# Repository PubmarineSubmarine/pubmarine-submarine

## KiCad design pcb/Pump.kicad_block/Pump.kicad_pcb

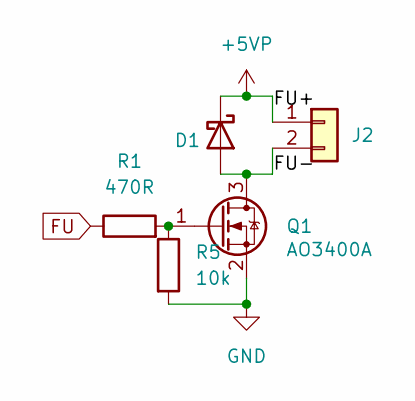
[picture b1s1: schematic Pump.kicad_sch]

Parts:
D1: B5819W; D_SOD-123
J2: Conn_01x02; JST_PH_B2B-PH-K_1x02_P2.00mm_Vertical
Q1: AO3400A; SOT-23_Handsoldering
R1: 470R; R_0603_1608Metric_Pad0.98x0.95mm_HandSolder
R5: 10k; R_0603_1608Metric_Pad0.98x0.95mm_HandSolder

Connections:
+5VP: D1.1 (K), J2.1
/FU-: D1.2 (A), J2.2, Q1.3 (D)
FU: R1.1
GND: Q1.2 (S), R5.2
unnamed: Q1.1 (G), R1.2, R5.1

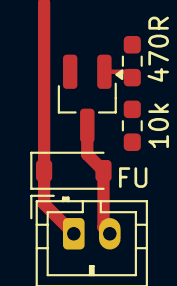
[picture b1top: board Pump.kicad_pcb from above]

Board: 2 copper layers, 5 parts (0 on the bottom side), 4 nets.

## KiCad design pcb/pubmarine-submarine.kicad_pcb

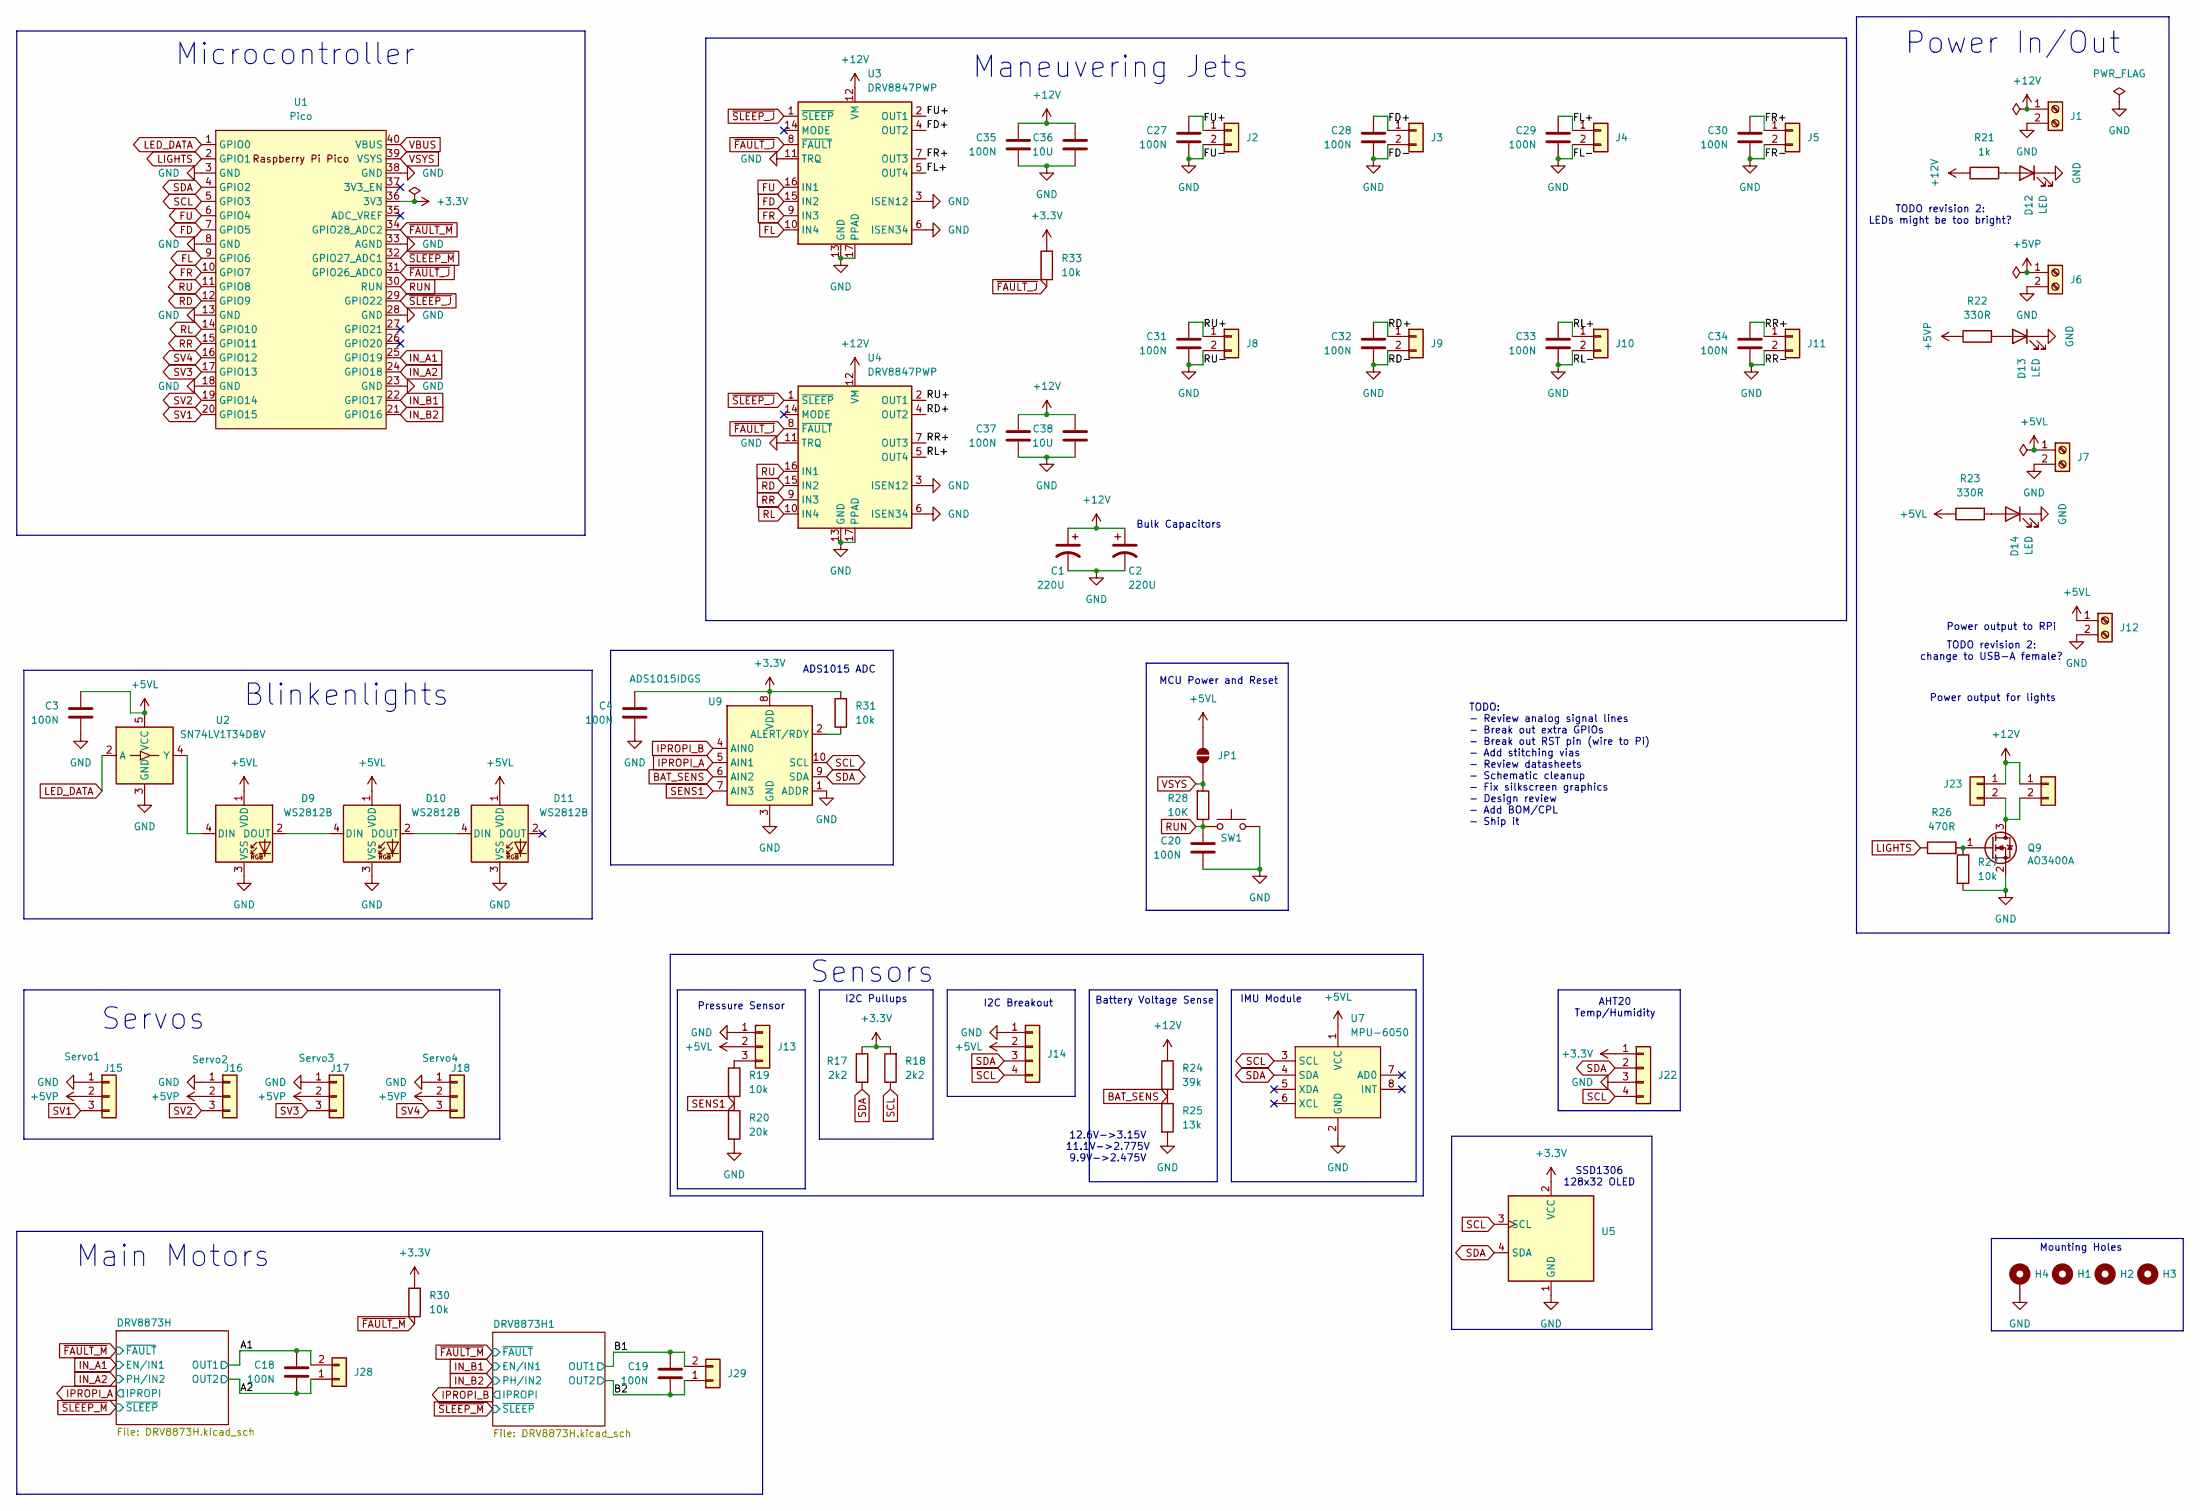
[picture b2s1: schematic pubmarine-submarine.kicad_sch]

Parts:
C1, C2: 220U; CP_Radial_D6.3mm_P2.50mm
C3, C4, C18, C19, C20, C27, C28, C29, C30, C31, C32, C33, C34, C35, C37: 100N; C_0603_1608Metric_Pad1.08x0.95mm_HandSolder
C36, C38: 10U; C_0603_1608Metric_Pad1.08x0.95mm_HandSolder
D9, D10, D11: WS2812B; LED_WS2812B_PLCC4_5.0x5.0mm_P3.2mm
D12, D13, D14: LED; LED_0603_1608Metric_Pad1.05x0.95mm_HandSolder
H1, H2, H3: MountingHole; MountingHole_2.2mm_M2
H4: MountingHole_Pad; MountingHole_2.2mm_M2_Pad
J1, J6, J7, J12: Screw_Terminal_01x02; TerminalBlock_Altech_AK300-2_P5.00mm
J2, J3, J4, J5, J8, J9, J10, J11, J23, J24: Conn_01x02; JST_PH_B2B-PH-K_1x02_P2.00mm_Vertical
J13: Conn_01x03; JST_PH_B3B-PH-K_1x03_P2.00mm_Vertical
J14: Conn_01x04; JST_PH_B4B-PH-K_1x04_P2.00mm_Vertical
J15: Servo1; JST_PH_B3B-PH-K_1x03_P2.00mm_Vertical
J16: Servo2; JST_PH_B3B-PH-K_1x03_P2.00mm_Vertical
J17: Servo3; JST_PH_B3B-PH-K_1x03_P2.00mm_Vertical
J18: Servo4; JST_PH_B3B-PH-K_1x03_P2.00mm_Vertical
J22: Conn_01x04; PinHeader_1x04_P2.54mm_Vertical
J28, J29: Conn_01x02; TerminalBlock_Altech_AK300-2_P5.00mm
JP1: Jumper_2_Open; SolderJumper-2_P1.3mm_Open_RoundedPad1.0x1.5mm
Q9: AO3400A; SOT-23_Handsoldering
R17, R18: 2k2; R_0603_1608Metric_Pad0.98x0.95mm_HandSolder
R19, R27, R30, R31, R33: 10k; R_0603_1608Metric_Pad0.98x0.95mm_HandSolder
R20: 20k; R_0603_1608Metric_Pad0.98x0.95mm_HandSolder
R21: 1k; R_0603_1608Metric_Pad0.98x0.95mm_HandSolder
R22, R23: 330R; R_0603_1608Metric_Pad0.98x0.95mm_HandSolder
R24: 39k; R_0603_1608Metric_Pad0.98x0.95mm_HandSolder
R25: 13k; R_0603_1608Metric_Pad0.98x0.95mm_HandSolder
R26: 470R; R_0603_1608Metric_Pad0.98x0.95mm_HandSolder
R28: 10K; R_0603_1608Metric_Pad0.98x0.95mm_HandSolder
SW1: SW_Push; SW_PUSH_6mm
U1: Pico; RPi_Pico_SMD_TH
U2: SN74LV1T34DBV; SOT-23-5
U3, U4: DRV8847PWP; HTSSOP-16-1EP_4.4x5mm_P0.65mm_EP3.4x5mm_Mask2.46x2.31mm_The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
U5: ER_OLEDM0.91_1x-I2C
U7: MPU-6050; MPU-6050_Module
U9: ADS1015IDGS; TSSOP-10_3x3mm_P0.5mm

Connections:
+5VP: J6.1, J15.2, J16.2, J17.2, J18.2, R22.1
+12V: C1.1, C2.1, C35.1, C36.1, C37.1, C38.1, J1.1, J23.1, J24.1, R21.1, R24.1, U3.12 (VM), U4.12 (VM); also elsewhere on the board
/A1: C18.1, J28.2; also elsewhere on the board
/A2: C18.2, J28.1; also elsewhere on the board
/B1: C19.1, J29.2; also elsewhere on the board
/B2: C19.2, J29.1; also elsewhere on the board
/FD+: C28.1, J3.1, U3.4 (OUT2)
/FL+: C29.1, J4.1, U3.5 (OUT4)
/FR+: C30.1, J5.1, U3.7 (OUT3)
/FU+: C27.1, J2.1, U3.2 (OUT1)
/RD+: C32.1, J9.1, U4.4 (OUT2)
/RL+: C33.1, J10.1, U4.5 (OUT4)
/RR+: C34.1, J11.1, U4.7 (OUT3)
/RU+: C31.1, J8.1, U4.2 (OUT1)
BAT_SENS: R24.2, R25.1, U9.6 (AIN2)
FD: U1.7 (GPIO5), U3.15 (IN2)
FL: U1.9 (GPIO6), U3.10 (IN4)
FR: U1.10 (GPIO7), U3.9 (IN3)
FU: U1.6 (GPIO4), U3.16 (IN1)
GND: C1.2, C2.2, C3.2, C4.2, C20.2, C27.2, C28.2, C29.2, C30.2, C31.2, C32.2, C33.2, C34.2, C35.2, C36.2, C37.2, C38.2, D9.3 (VSS), D10.3 (VSS), D11.3 (VSS), D12.1 (K), D13.1 (K), D14.1 (K), H4.1 (1_1), J1.2, J2.2, J3.2, J4.2, J5.2, J6.2, J7.2, J8.2, J9.2, J10.2, J11.2, J12.2, J13.1, J14.1, J15.1, J16.1, J17.1, J18.1, J22.3, Q9.2 (S), R20.2, R25.2, R27.2, SW1.2, U1.3 (GND), U1.8 (GND), U1.13 (GND), U1.18 (GND), U1.23 (GND), U1.28 (GND), U1.33 (AGND), U1.38 (GND), U2.3 (GND), U3.3 (ISEN12), U3.6 (ISEN34), U3.11 (TRQ), U3.13 (GND), U3.17 (PPAD), U4.3 (ISEN12), U4.6 (ISEN34), U4.11 (TRQ), U4.13 (GND), U4.17 (PPAD), U5.1 (GND), U7.2 (GND), U9.1 (ADDR), U9.3 (GND); also elsewhere on the board
IN_A1: U1.25 (GPIO19); also elsewhere on the board
IN_A2: U1.24 (GPIO18); also elsewhere on the board
IN_B1: U1.22 (GPIO17); also elsewhere on the board
IN_B2: U1.21 (GPIO16); also elsewhere on the board
IPROPI_A: U9.5 (AIN1); also elsewhere on the board
IPROPI_B: U9.4 (AIN0); also elsewhere on the board
LED_DATA: U1.1 (GPIO0), U2.2 (A)
LIGHTS: R26.1, U1.2 (GPIO1)
unnamed: D9.4 (DIN), U2.4 (Y)
unnamed: D9.2 (DOUT), D10.4 (DIN)
unnamed: D10.2 (DOUT), D11.4 (DIN)
unnamed: D12.2 (A), R21.2
unnamed: D13.2 (A), R22.2
unnamed: D14.2 (A), R23.2
unnamed: J13.3, R19.1
unnamed 37: U1.32 (GPIO27_ADC1); also elsewhere on the board
unnamed: J23.2, J24.2, Q9.3 (D)
unnamed: Q9.1 (G), R26.2, R27.1
unnamed: R31.1, U9.2 (ALERT/RDY)
RD: U1.12 (GPIO9), U4.15 (IN2)
RL: U1.14 (GPIO10), U4.10 (IN4)
RR: U1.15 (GPIO11), U4.9 (IN3)
RU: U1.11 (GPIO8), U4.16 (IN1)
RUN: C20.1, R28.1, SW1.1, U1.30 (RUN); also elsewhere on the board
SCL: J14.4, J22.4, R18.1, U1.5 (GPIO3), U5.3 (SCL), U7.3 (SCL), U9.10 (SCL)
SDA: J14.3, J22.2, R17.1, U1.4 (GPIO2), U5.4 (SDA), U7.4 (SDA), U9.9 (SDA)
SENS1: R19.2, R20.1, U9.7 (AIN3)
SV1: J15.3, U1.20 (GPIO15)
SV2: J16.3, U1.19 (GPIO14)
SV3: J17.3, U1.17 (GPIO13)
SV4: J18.3, U1.16 (GPIO12)
VBUS: U1.40 (VBUS)
VSYS: JP1.1 (A), R28.2, U1.39 (VSYS)
~FAULT_M: R30.2, U1.34 (GPIO28_ADC2); also elsewhere on the board

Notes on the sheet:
TODO revision 2: LEDs might be too bright?
Pressure Sensor
Bulk Capacitors
Sensors
ADS1015 ADC
Power output to RPi
TODO: - Review analog signal lines - Break out extra GPIOs - Break out RST pin (wire to Pi) - Add stitching vias - Review datasheets - Schematic cleanup - Fix silkscreen graphics - Design review - Add BOM/CPL - Ship it
IMU Module
Main Motors
I2C Breakout
MCU Power and Reset
Servos
Battery Voltage Sense
SSD1306 128x32 OLED
Power In/Out
I2C Pullups
Microcontroller
12.6V->3.15V 11.1V->2.775V 9.9V->2.475V
TODO revision 2: change to USB-A female?
AHT20 Temp/Humidity
Mounting Holes
Maneuvering Jets
Power output for lights
Blinkenlights

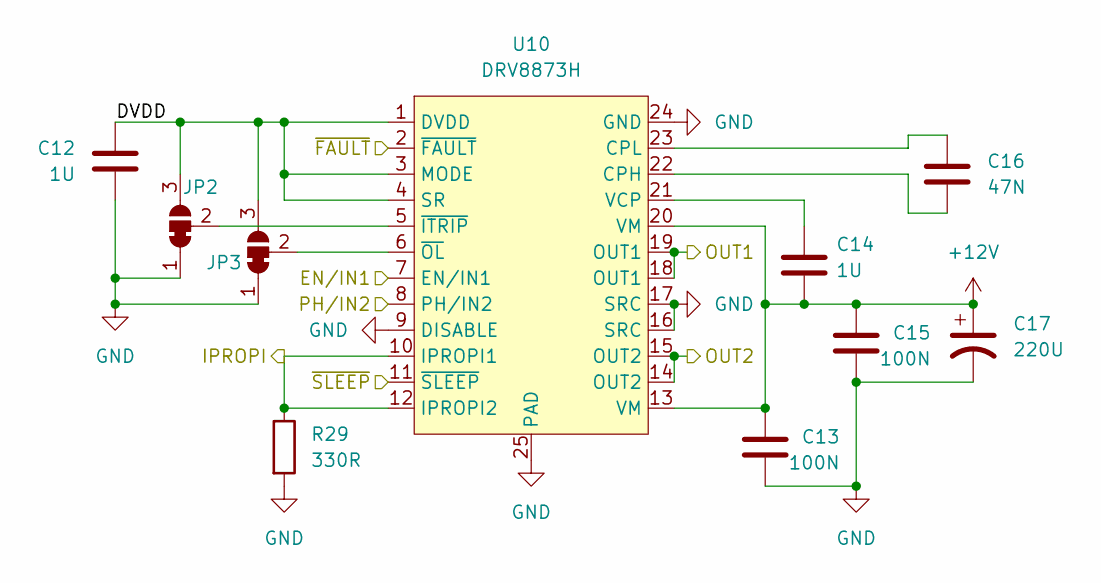
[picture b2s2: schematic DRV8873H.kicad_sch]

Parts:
C12, C14: 1U; C_0603_1608Metric_Pad1.08x0.95mm_HandSolder
C13, C15: 100N; C_0603_1608Metric_Pad1.08x0.95mm_HandSolder
C16: 47N; C_0603_1608Metric_Pad1.08x0.95mm_HandSolder
C17: 220U; CP_Radial_D6.3mm_P2.50mm
JP2, JP3: SolderJumper_3_Bridged12; SolderJumper-3_P1.3mm_Bridged12_RoundedPad1.0x1.5mm
R29: 330R; R_0603_1608Metric_Pad0.98x0.95mm_HandSolder
U10: DRV8873H; HTSSOP-24-1EP_4.4x7.8mm_P0.65mm_EP3.4x7.8mm_Mask2.44x3.42mm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

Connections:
+12V: C13.1, C14.2, C15.1, C17.1, U10.13 (VM), U10.20 (VM); also elsewhere on the board
/A1: U10.18 (OUT1), U10.19 (OUT1); also elsewhere on the board
/A2: U10.14 (OUT2), U10.15 (OUT2); also elsewhere on the board
/DRV8873H/DVDD: C12.1, JP2.3 (B), JP3.3 (B), U10.1 (DVDD), U10.3 (MODE), U10.4 (SR)
GND: C12.2, C13.2, C15.2, C17.2, JP2.1 (A), JP3.1 (A), R29.2, U10.9 (DISABLE), U10.16 (SRC), U10.17 (SRC), U10.24 (GND), U10.25 (PAD); also elsewhere on the board
IN_A1: U10.7 (EN/IN1); also elsewhere on the board
IN_A2: U10.8 (PH/IN2); also elsewhere on the board
IPROPI_A: R29.1, U10.10 (IPROPI1), U10.12 (IPROPI2); also elsewhere on the board
unnamed: JP2.2 (C), U10.5 (~ITRIP)
unnamed: JP3.2 (C), U10.6 (~OL)
unnamed: C16.2, U10.22 (CPH)
unnamed: C16.1, U10.23 (CPL)
unnamed: C14.1, U10.21 (VCP)
~FAULT_M: U10.2 (~FAULT); also elsewhere on the board

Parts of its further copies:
C21, C23: 1U; C_0603_1608Metric_Pad1.08x0.95mm_HandSolder
C22, C24: 100N; C_0603_1608Metric_Pad1.08x0.95mm_HandSolder
C25: 47N; C_0603_1608Metric_Pad1.08x0.95mm_HandSolder
C26: 220U; CP_Radial_D6.3mm_P2.50mm
JP4, JP5: SolderJumper_3_Bridged12; SolderJumper-3_P1.3mm_Bridged12_RoundedPad1.0x1.5mm
R32: 330R; R_0603_1608Metric_Pad0.98x0.95mm_HandSolder
U11: DRV8873H; HTSSOP-24-1EP_4.4x7.8mm_P0.65mm_EP3.4x7.8mm_Mask2.44x3.42mm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

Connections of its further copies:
+12V: C22.1, C23.2, C24.1, C26.1, U11.13 (VM), U11.20 (VM); also elsewhere on the board
/B1: U11.18 (OUT1), U11.19 (OUT1); also elsewhere on the board
/B2: U11.14 (OUT2), U11.15 (OUT2); also elsewhere on the board
/DRV8873H1/DVDD: C21.1, JP4.3 (B), JP5.3 (B), U11.1 (DVDD), U11.3 (MODE), U11.4 (SR)
GND: C21.2, C22.2, C24.2, C26.2, JP4.1 (A), JP5.1 (A), R32.2, U11.9 (DISABLE), U11.16 (SRC), U11.17 (SRC), U11.24 (GND), U11.25 (PAD); also elsewhere on the board
IN_B1: U11.7 (EN/IN1); also elsewhere on the board
IN_B2: U11.8 (PH/IN2); also elsewhere on the board
IPROPI_B: R32.1, U11.10 (IPROPI1), U11.12 (IPROPI2); also elsewhere on the board
unnamed: JP4.2 (C), U11.5 (~ITRIP)
unnamed: JP5.2 (C), U11.6 (~OL)
unnamed: C25.2, U11.22 (CPH)
unnamed: C25.1, U11.23 (CPL)
unnamed: C23.1, U11.21 (VCP)
~FAULT_M: U11.2 (~FAULT); also elsewhere on the board

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
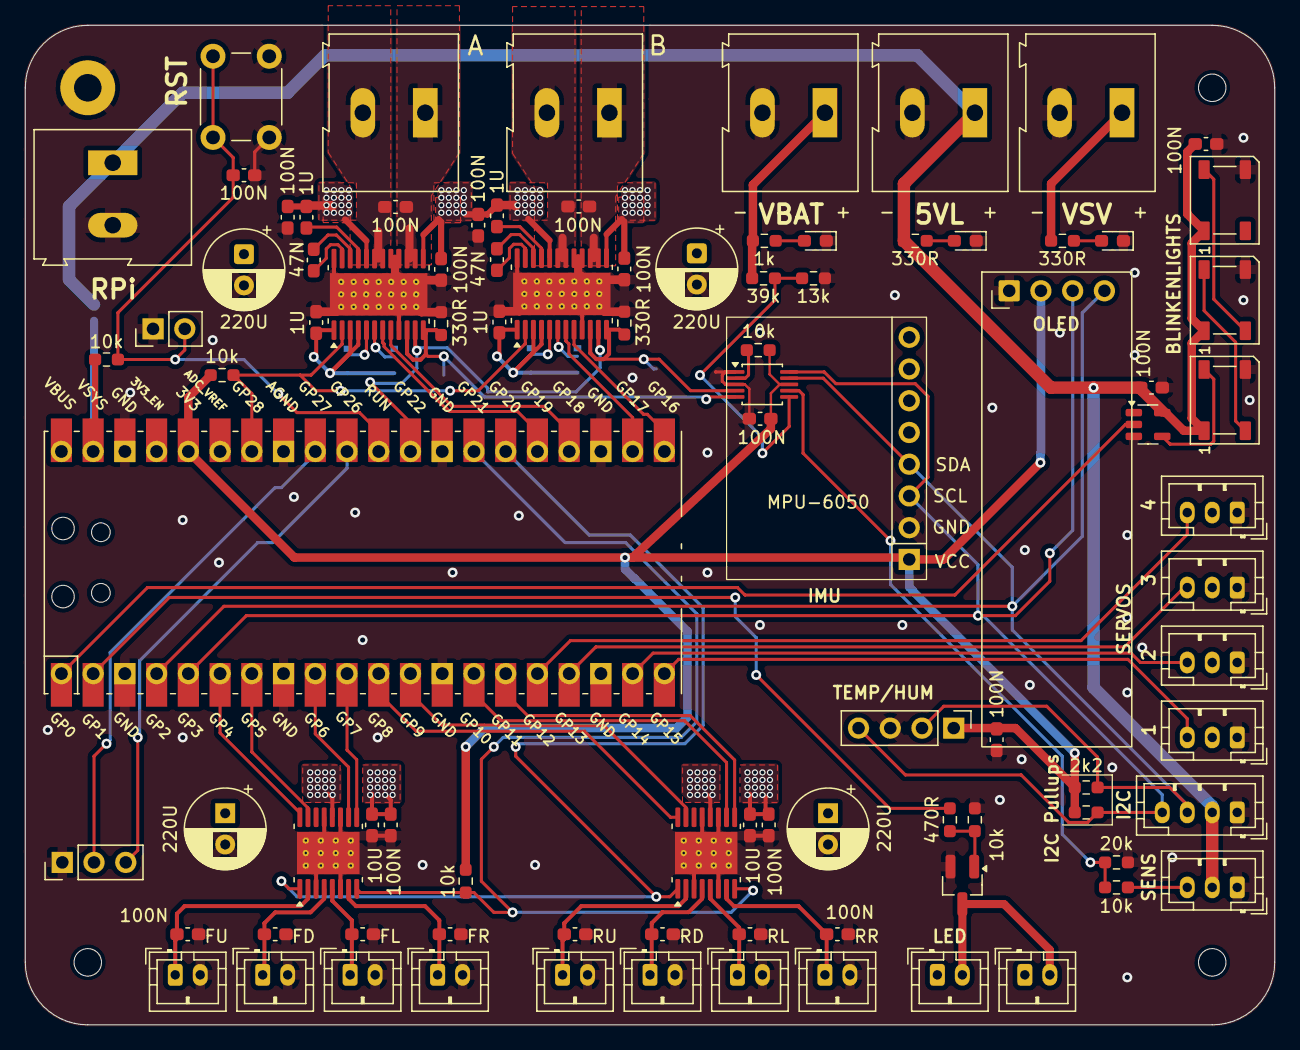
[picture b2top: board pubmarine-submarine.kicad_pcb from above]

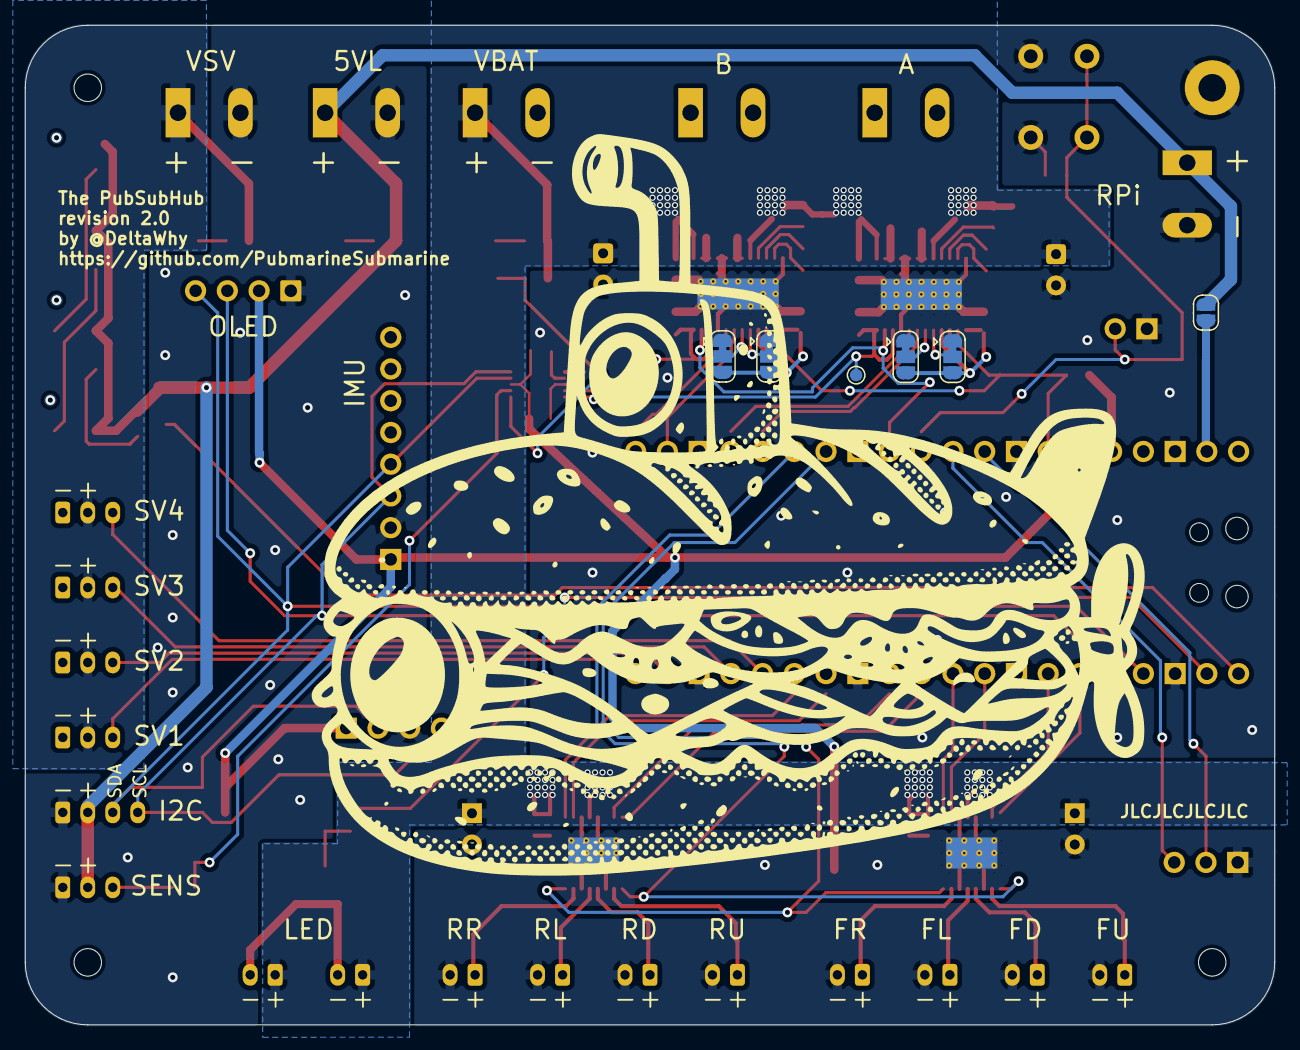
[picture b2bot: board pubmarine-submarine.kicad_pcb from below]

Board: 4 copper layers, 100.0 x 80.0 mm, 103 parts (7 on the bottom side), 71 nets.

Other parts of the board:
C5, C6: 100N; C_0603_1608Metric_Pad1.08x0.95mm_HandSolder
J19: Conn_01x03_Pin; PinHeader_1x03_P2.54mm_Vertical
J20: Conn_01x02_Pin; PinHeader_1x02_P2.54mm_Vertical
TP1, TP2: TestPoint; TestPoint_Pad_D1.0mm

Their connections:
GND: C5.2, C6.2, J19.1, J20.1; also elsewhere on the board
IPROPI_A: TP1.1 (1_1); also elsewhere on the board
IPROPI_B: TP2.1 (1_1); also elsewhere on the board
unnamed 37: J19.2; also elsewhere on the board
RUN: J20.2; also elsewhere on the board

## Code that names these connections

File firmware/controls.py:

import board
import pins

import analogio
import digitalio
import pwmio
import busio
import neopixel
import adafruit_mpu6050_patched as adafruit_mpu6050
import adafruit_ads1x15.ads1015
import adafruit_ads1x15.analog_in
import adafruit_ahtx0
import displayio
import i2cdisplaybus
import adafruit_displayio_ssd1306

from adafruit_motor import motor, servo
from config import get_config


# Main motors
_a1 = pwmio.PWMOut(pins.A1, frequency=10000)
_a2 = pwmio.PWMOut(pins.A2, frequency=10000)
_b1 = pwmio.PWMOut(pins.B1, frequency=10000)
_b2 = pwmio.PWMOut(pins.B2, frequency=10000)
motor_a = motor.DCMotor(_a1, _a2)
motor_b = motor.DCMotor(_b1, _b2)
motor_a.decay_mode = motor.FAST_DECAY
motor_b.decay_mode = motor.FAST_DECAY
sleep_m = digitalio.DigitalInOut(pins.SLEEP_M)
sleep_m.switch_to_output()
fault_m = digitalio.DigitalInOut(pins.FAULT_M)
fault_m.switch_to_input()

# Jets
_jet_mapping = get_config().get("jet_mapping", "ABCDEFGH")
_pin_mapping = {"A": pins.FU, "B": pins.FD, "C": pins.FL, "D": pins.FR,
                "E": pins.RU, "F": pins.RD, "G": pins.RL, "H": pins.RR}
jet_fu = digitalio.DigitalInOut(_pin_mapping[_jet_mapping[0]])
jet_fu.switch_to_output()
jet_fd = digitalio.DigitalInOut(_pin_mapping[_jet_mapping[1]])
jet_fd.switch_to_output()
jet_fl = digitalio.DigitalInOut(_pin_mapping[_jet_mapping[2]])
jet_fl.switch_to_output()
jet_fr = digitalio.DigitalInOut(_pin_mapping[_jet_mapping[3]])
jet_fr.switch_to_output()
jet_ru = digitalio.DigitalInOut(_pin_mapping[_jet_mapping[4]])
jet_ru.switch_to_output()
jet_rd = digitalio.DigitalInOut(_pin_mapping[_jet_mapping[5]])
jet_rd.switch_to_output()
jet_rl = digitalio.DigitalInOut(_pin_mapping[_jet_mapping[6]])
jet_rl.switch_to_output()
jet_rr = digitalio.DigitalInOut(_pin_mapping[_jet_mapping[7]])
jet_rr.switch_to_output()
sleep_j = digitalio.DigitalInOut(pins.SLEEP_J)
sleep_j.switch_to_output()
fault_j = digitalio.DigitalInOut(pins.FAULT_J)
fault_j.switch_to_input()

# Servos
_sv1 = pwmio.PWMOut(pins.SV1, frequency=50, duty_cycle=0)
sv1 = servo.Servo(_sv1, min_pulse=500, max_pulse=2500, actuation_range=180)
_sv2 = pwmio.PWMOut(pins.SV2, frequency=50, duty_cycle=0)
sv2 = servo.Servo(_sv2, min_pulse=500, max_pulse=2500, actuation_range=180)
_sv3 = pwmio.PWMOut(pins.SV3, frequency=50, duty_cycle=0)
sv3 = servo.Servo(_sv3, min_pulse=500, max_pulse=2500, actuation_range=180)
_sv4 = pwmio.PWMOut(pins.SV4, frequency=50, duty_cycle=0)
sv4 = servo.Servo(_sv4, min_pulse=500, max_pulse=2500, actuation_range=180)

lights = digitalio.DigitalInOut(pins.LIGHTS)
lights.switch_to_output()

# WS2812B
pixels = neopixel.NeoPixel(pins.LED_DATA, 3)
led = digitalio.DigitalInOut(board.LED)
led.switch_to_output()

# I2C/MPU6050
displayio.release_displays()
i2c = busio.I2C(pins.SCL, pins.SDA, frequency=400000)
mpu = adafruit_mpu6050.MPU6050(i2c)
try:
    ads = adafruit_ads1x15.ads1015.ADS1015(i2c, gain=1, data_rate=1600, mode=adafruit_ads1x15.ads1x15.Mode.SINGLE)
    aht = adafruit_ahtx0.AHTx0(i2c)
    display_bus = i2cdisplaybus.I2CDisplayBus(i2c, device_address=0x3c)
    display = adafruit_displayio_ssd1306.SSD1306(display_bus, width=128, height=32, auto_refresh=False)

    # Analog sensors
    sensor_depth = adafruit_ads1x15.analog_in.AnalogIn(ads, adafruit_ads1x15.ads1015.P3)
    sensor_battery = adafruit_ads1x15.analog_in.AnalogIn(ads, adafruit_ads1x15.ads1015.P2)
    sensor_ipropi_a = adafruit_ads1x15.analog_in.AnalogIn(ads, adafruit_ads1x15.ads1015.P1)
    sensor_ipropi_b = adafruit_ads1x15.analog_in.AnalogIn(ads, adafruit_ads1x15.ads1015.P0)
except ValueError as e:
    import traceback
    traceback.print_exception(e)
    print("Falling back to mocks")
    from mock_controls import *

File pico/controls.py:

import board
import pins

import analogio
import digitalio
import pwmio
import busio
import neopixel
import adafruit_mpu6050

from adafruit_motor import motor, servo


# Main motors
# Motor W is unusable on board revision 1 due to a PWM channel conflict
_x1 = pwmio.PWMOut(pins.X1, frequency=440)
_x2 = pwmio.PWMOut(pins.X2, frequency=440)
_y1 = pwmio.PWMOut(pins.Y1, frequency=440)
_y2 = pwmio.PWMOut(pins.Y2, frequency=440)
_z1 = pwmio.PWMOut(pins.Z1, frequency=440)
_z2 = pwmio.PWMOut(pins.Z2, frequency=440)
# _w1 = pwmio.PWMOut(pins.W1, frequency=440)
# _w2 = pwmio.PWMOut(pins.W2, frequency=440)
motor_x = motor.DCMotor(_x1, _x2)
motor_y = motor.DCMotor(_y1, _y2)
motor_z = motor.DCMotor(_z1, _z2)
# motor_w = motor.DCMotor(_w1, _w2)
motor_x.decay_mode = motor.FAST_DECAY
motor_y.decay_mode = motor.FAST_DECAY
motor_z.decay_mode = motor.FAST_DECAY
# motor_w.decay_mode = motor.FAST_DECAY

# Jets
jet_fu = digitalio.DigitalInOut(pins.FU)
jet_fu.switch_to_output()
jet_fd = digitalio.DigitalInOut(pins.FD)
jet_fd.switch_to_output()
jet_fl = digitalio.DigitalInOut(pins.FL)
jet_fl.switch_to_output()
jet_fr = digitalio.DigitalInOut(pins.FR)
jet_fr.switch_to_output()
jet_ru = digitalio.DigitalInOut(pins.RU)
jet_ru.switch_to_output()
jet_rd = digitalio.DigitalInOut(pins.RD)
jet_rd.switch_to_output()
jet_rl = digitalio.DigitalInOut(pins.RL)
jet_rl.switch_to_output()
jet_rr = digitalio.DigitalInOut(pins.RR)
jet_rr.switch_to_output()

# Servos
# TODO
_sv1 = pwmio.PWMOut(pins.SV1, frequency=50, duty_cycle=0)
sv1 = servo.Servo(_sv1, min_pulse=500, max_pulse=2500, actuation_range=180)
_sv2 = pwmio.PWMOut(pins.SV2, frequency=50, duty_cycle=0)
sv2 = servo.Servo(_sv2, min_pulse=500, max_pulse=2500, actuation_range=180)
_sv3 = pwmio.PWMOut(pins.SV3, frequency=50, duty_cycle=0)
sv3 = servo.Servo(_sv3, min_pulse=500, max_pulse=2500, actuation_range=180)
_sv4 = pwmio.PWMOut(pins.SV4, frequency=50, duty_cycle=0)
sv4 = servo.Servo(_sv4, min_pulse=500, max_pulse=2500, actuation_range=180)

# WS2812B
pixels = neopixel.NeoPixel(pins.LED_DATA, 3)
led = digitalio.DigitalInOut(board.LED)
led.switch_to_output()

# I2C/MPU6050
# try:
#     i2c = busio.I2C(pins.SCL, pins.SDA)
#     mpu = adafruit_mpu6050.MPU6050(i2c)
# except Exception as e:
#     import traceback
#     traceback.print_exception(e)

# Analog sensors
sensor_depth = analogio.AnalogIn(pins.SENS1)
sensor_battery = analogio.AnalogIn(pins.BAT_SENS)

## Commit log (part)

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2025-07-02 initial demo
2025-07-02 video preview improved
2025-07-05 clean up and fixes
2025-07-05 not needed
2025-07-05 more delete
2025-07-12 new PCB
2025-07-13 pcb updates
2025-07-18 pcb update
2025-07-25 pcb: IMU breakout and silkscreen cleanup
2025-07-27 silkscreen updates
2025-07-30 pcb: fix clearances
2025-08-07 descuff camera
2025-08-07 take 1
2025-08-10 iframe
2025-08-10 firmware start
2025-08-10 parser and start of serial client
2025-08-11 more proto
2025-08-11 websocket buttons
2025-08-12 plumbing
2025-08-14 pcb: fix LSS pins, notes for other rev2 changes
2025-08-23 firmware: servo control
2025-08-24 software: analog triggers, serial fixes
2025-08-24 software: limit servo range to +/-45deg
2025-08-24 firmware: motor and servo control, status protocol
2025-08-26 whatever I didn't have pushed
2025-08-27 send full gamepad state to python & implement serial retries
2025-08-29 gpio reset
2025-08-29 give each message its own task
2025-08-30 firmware: error handling, fix stop command
2025-08-30 mediamtx config
2025-10-05 sub 3d preview
2025-10-05 sub preview looks better
2025-12-01 fullscreen preview + artificial horizon
2026-01-22 file dump
2026-04-25 pcb v2 wip
2026-04-26 wip: PCB rev2, motors mostly done?
2026-04-27 wip pcb
2026-04-27 pcb rev2 done?
2026-04-27 web serial console
2026-04-27 pcb tweaks
2026-04-27 repr in debug client not plumbing
2026-05-04 pcb: 1oz copper
2026-05-17 control remap
2026-05-17 rev2 updates
2026-05-17 integrate changes from April
2026-05-22 Michael's commit
2026-05-23 fix serial read lag
2026-05-29 live tweaks (idk who made these)
2026-05-29 serial reconnect take 2
2026-05-29 serial port env
2026-05-30 lint python
2026-05-30 fix frontend slowdown
2026-05-30 lint gamepad.js
2026-06-03 convert to preact
2026-06-05 cleanup
2026-06-11 fixed some bugs
2026-06-12 more cleanup
2026-06-12 convert the rest of the stuff to preact
2026-06-12 don't delete gpio & delete some more code
2026-06-12 remove some comment spam
2026-06-12 update readme for backend hot reload
2026-06-15 first pass
2026-06-16 css updatE
2026-06-16 UI tweaks + start button console toggle
2026-06-16 idk I just found this here
2026-06-17 live debugging
2026-06-17 python imports are hard
2026-06-17 un-invert pitch
2026-06-17 clean up exceptions
2026-06-17 hopefully fix background crash
2026-06-17 npm run build
2026-06-17 wrap on console
2026-06-17 console
2026-06-24 heartbeat + console bugfix
2026-06-24 heartbeat toggle on console too
2026-06-27 jet test, jet mapping, soft servo control
